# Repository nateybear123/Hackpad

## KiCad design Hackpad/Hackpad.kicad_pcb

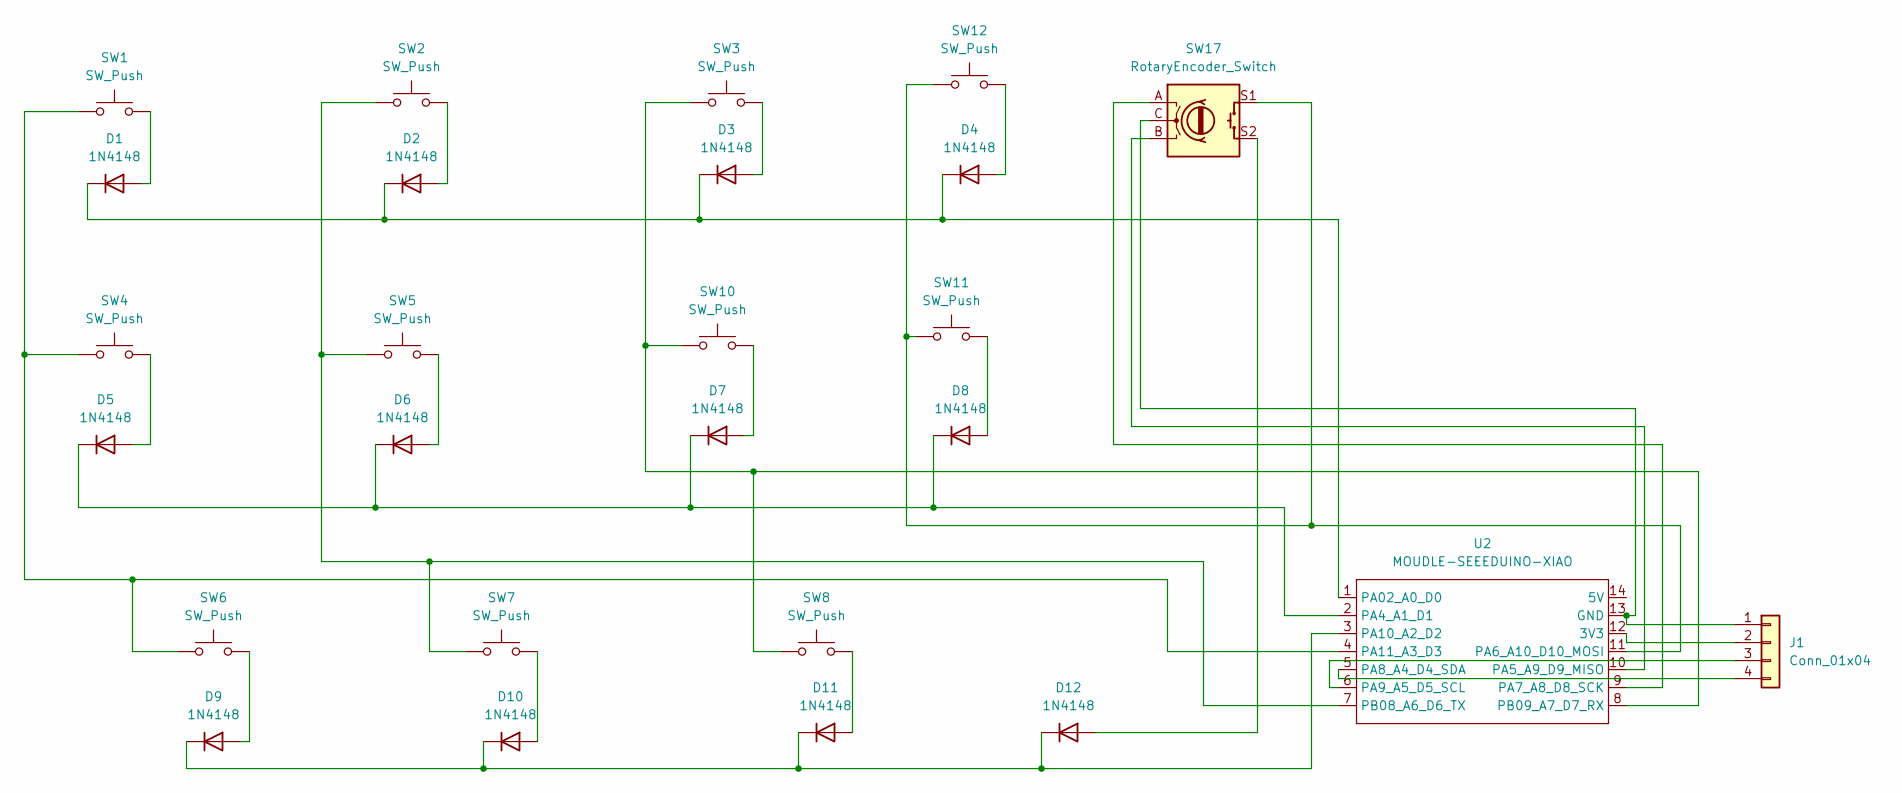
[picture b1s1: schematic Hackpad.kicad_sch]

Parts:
D1, D2, D3, D4, D5, D6, D7, D8, D9, D10, D11, D12: 1N4148; D_DO-35_SOD27_P7.62mm_Horizontal
J1: Conn_01x04; PinHeader_1x04_P2.54mm_Vertical
SW1, SW2, SW3, SW4, SW5, SW6, SW7, SW8, SW10, SW11, SW12: SW_Push; SW_Cherry_MX_1.00u_PCB
SW17: RotaryEncoder_Switch; RotaryEncoder_Alps_EC11E-Switch_Vertical_H20mm
U2: MOUDLE-SEEEDUINO-XIAO; XIAO-Generic-Hybrid-14P-2.54-21X17.8MM

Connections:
unnamed: D1.2 (A), SW1.2
unnamed: D1.1 (K), D2.1 (K), D3.1 (K), D4.1 (K), U2.1 (PA02_A0_D0)
unnamed: D2.2 (A), SW2.2
unnamed: D3.2 (A), SW3.2
unnamed: D4.2 (A), SW12.2
unnamed: D5.2 (A), SW4.2
unnamed: D5.1 (K), D6.1 (K), D7.1 (K), D8.1 (K), U2.2 (PA4_A1_D1)
unnamed: D6.2 (A), SW5.2
unnamed: D7.2 (A), SW10.2
unnamed: D8.2 (A), SW11.2
unnamed: D9.2 (A), SW6.2
unnamed: D10.2 (A), SW7.2
unnamed: D9.1 (K), D10.1 (K), D11.1 (K), D12.1 (K), U2.3 (PA10_A2_D2)
unnamed: D11.2 (A), SW8.2
unnamed: D12.2 (A), SW17.S2
unnamed: J1.1, SW17.C, U2.13 (GND)
unnamed: J1.2, U2.12 (3V3)
unnamed: J1.3, U2.6 (PA9_A5_D5_SCL)
unnamed: J1.4, U2.5 (PA8_A4_D4_SDA)
unnamed: SW17.B, U2.10 (PA5_A9_D9_MISO)
unnamed: SW11.1, SW12.1, SW17.S1, U2.11 (PA6_A10_D10_MOSI)
unnamed: SW17.A, U2.9 (PA7_A8_D8_SCK)
unnamed: SW1.1, SW4.1, SW6.1, U2.4 (PA11_A3_D3)
unnamed: SW2.1, SW5.1, SW7.1, U2.7 (PB08_A6_D6_TX)
unnamed: SW3.1, SW8.1, SW10.1, U2.8 (PB09_A7_D7_RX)

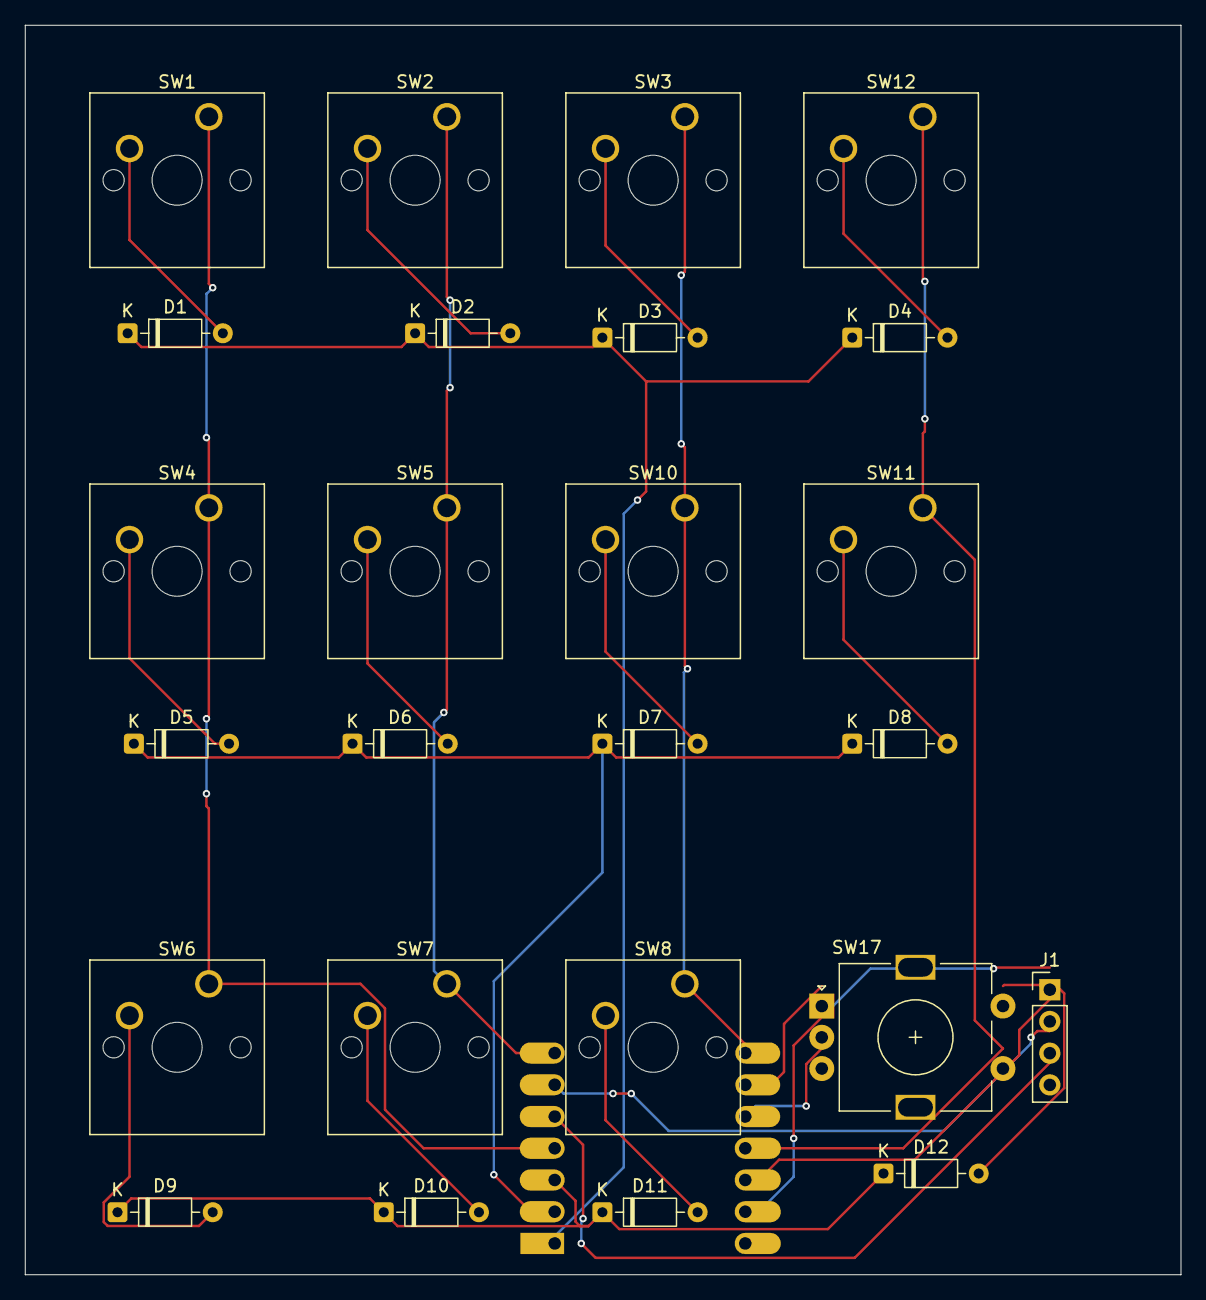
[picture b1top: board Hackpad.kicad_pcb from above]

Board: 2 copper layers, 92.5 x 100.0 mm, 26 parts (1 on the bottom side), 25 nets.

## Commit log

2026-06-07 Initial Push
2026-06-07 Push Kicad files
2026-06-07 Rename Hackpad Code/README.md to README.md
    Move README from 'Hackpad Code/README.md' to the repository root as 'README.md'. No content changes (similarity 100%).
